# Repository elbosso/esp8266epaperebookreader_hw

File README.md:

# esp8266epaperebookreader_hw
hardware for an (cloud-based) ebook-reader (https://github.com/elbosso/esp8266epaperebookreader)

<!---

--->

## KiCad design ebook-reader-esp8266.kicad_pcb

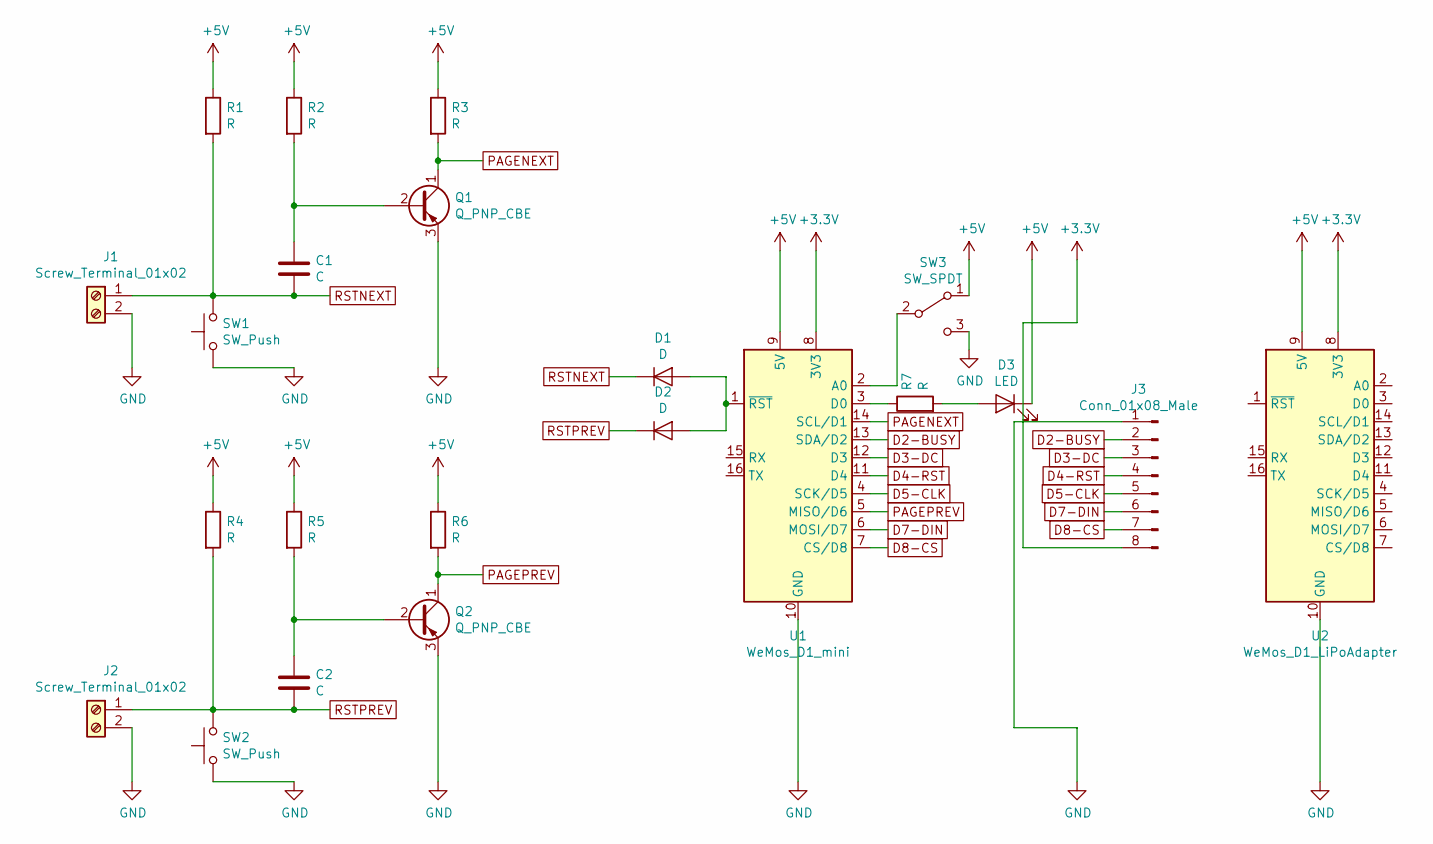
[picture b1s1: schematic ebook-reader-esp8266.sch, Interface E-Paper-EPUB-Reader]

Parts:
C1, C2: C; C_Disc_D5.0mm_W2.5mm_P5.00mm
D1, D2: D; D_A-405_P2.54mm_Vertical_AnodeUp
D3: LED; LED_D3.0mm
J1, J2: Screw_Terminal_01x02; TerminalBlock_Altech_AK300-2_P5.00mm
J3: Conn_01x08_Male; PinHeader_1x08_P2.54mm_Horizontal
Q1, Q2: Q_PNP_CBE; TO-92_Inline
R1, R2, R3, R4, R5, R6, R7: R; R_Axial_DIN0207_L6.3mm_D2.5mm_P7.62mm_Horizontal
SW1, SW2: SW_Push; SW_PUSH_6mm
SW3: SW_SPDT; PinHeader_1x03_P2.54mm_Vertical
U1: WeMos_D1_mini; WEMOS_D1_mini_light
U2: WeMos_D1_LiPoAdapter; WEMOS_D1_mini_light

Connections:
+3V3: J3.8, U1.8 (3V3), U2.8 (3V3)
+5V: D3.1 (K), R1.1, R2.1, R3.1, R4.1, R5.1, R6.1, SW3.1 (A), U1.9 (5V), U2.9 (5V)
D2-BUSY: J3.2, U1.13 (SDA/D2)
D3-DC: J3.3, U1.12 (D3)
D4-RST: J3.4, U1.11 (D4)
D5-CLK: J3.5, U1.4 (SCK/D5)
D7-DIN: J3.6, U1.6 (MOSI/D7)
D8-CS: J3.7, U1.7 (CS/D8)
GND: J1.2, J2.2, J3.1, Q1.3 (E), Q2.3 (E), SW1.1, SW2.1, SW3.3 (C), U1.10 (GND), U2.10 (GND)
unnamed: C1.1, Q1.2 (B), R2.2
unnamed: C2.1, Q2.2 (B), R5.2
unnamed: D1.2 (A), D2.2 (A), U1.1 (~RST)
unnamed: D3.2 (A), R7.2
unnamed: R7.1, U1.3 (D0)
unnamed: SW3.2 (B), U1.2 (A0)
PAGENEXT: Q1.1 (C), R3.2, U1.14 (SCL/D1)
PAGEPREV: Q2.1 (C), R6.2, U1.5 (MISO/D6)
RSTNEXT: C1.2, D1.1 (K), J1.1, R1.2, SW1.2
RSTPREV: C2.2, D2.1 (K), J2.1, R4.2, SW2.2

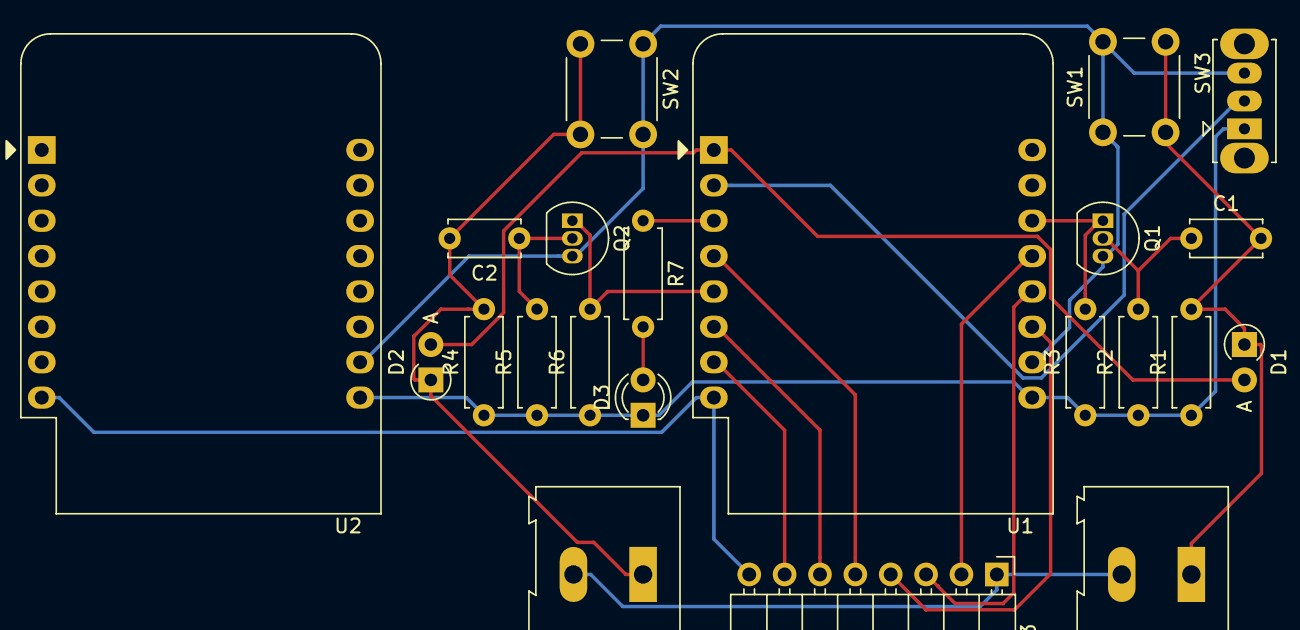
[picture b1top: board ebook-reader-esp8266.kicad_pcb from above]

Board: 2 copper layers, 22 parts (0 on the bottom side), 19 nets.
